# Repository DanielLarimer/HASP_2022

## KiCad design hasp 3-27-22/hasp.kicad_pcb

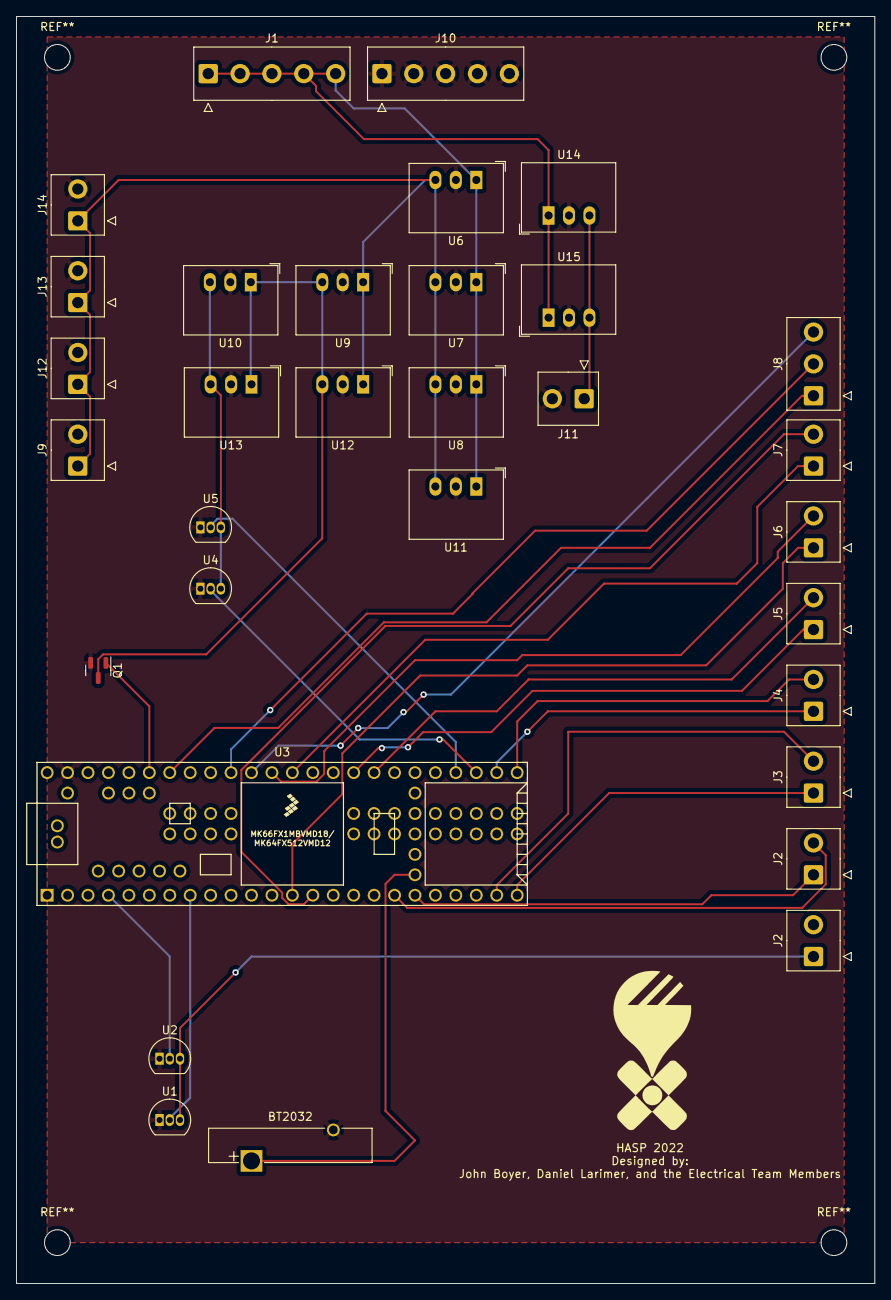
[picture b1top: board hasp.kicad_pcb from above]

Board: 2 copper layers, 106.7 x 157.5 mm, 33 parts (0 on the bottom side), 27 nets.

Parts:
 : LOGO; HASP 2022 KICAD
BT2032: Battery_Cell; Battery_Panasonic_CR2032-VS1N_Vertical_CircularHoles
J1, J10: Conn_01x05; TE_826576-5_1x05_P3.96mm_Vertical
J2, J2#2, J3, J4, J5, J6, J7: Conn_01x02; TE_826576-2_1x02_P3.96mm_Vertical
J8: Conn_01x03; TE_826576-3_1x03_P3.96mm_Vertical
J9: cam 1 Con; TE_826576-2_1x02_P3.96mm_Vertical
J11, J14: Cam 4 Con; TE_826576-2_1x02_P3.96mm_Vertical
J12: Cam 2 Con; TE_826576-2_1x02_P3.96mm_Vertical
J13: Cam 3 Con; TE_826576-2_1x02_P3.96mm_Vertical
Q1: BC818; SOT-23
U1, U2, U4, U5: DS18B20; TO-92_Inline
U3: Teensy3.6; Teensy35_36_All_Pins
U6, U7, U8, U11: R-78E12-0.5; Converter_DCDC_RECOM_R-78E-0.5_THT
U9, U12, U14, U15: R-78C5.0-1.0; Converter_DCDC_RECOM_R-78E-0.5_THT
U10, U13: R-78E3.3-1.0; Converter_DCDC_RECOM_R-78E-0.5_THT

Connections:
+3V3: J2.1, U1.3 (VDD), U2.3 (VDD), U4.3 (VDD), U5.3 (VDD), U10.3 (OUT), U13.3 (OUT)
+5V: J2.2, Q1.3 (C), U3.53 (VIN), U9.3 (OUT), U10.1 (IN), U12.3 (OUT), U13.1 (IN)
+12V: J9.1, J12.1, J13.1, J14.1, U6.3 (OUT), U7.3 (OUT), U8.3 (OUT), U9.1 (IN), U11.3 (OUT), U12.1 (IN)
+VDC: J1.1, J1.2, J1.3, J1.4, J1.5, U6.1 (IN), U7.1 (IN), U8.1 (IN), U11.1 (IN), U14.1 (IN), U15.1 (IN)
GND: BT2032.2 (-), J9.2, J10.1, J10.2, J10.3, J10.4, J10.5, J11.2, J12.2, J13.2, J14.2, Q1.2 (E), U1.1 (GND), U2.1 (GND), U3.1 (GND), U3.52 (AGND), U4.1 (GND), U5.1 (GND), U6.2 (GND), U7.2 (GND), U8.2 (GND), U9.2 (GND), U10.2 (GND), U11.2 (GND), U12.2 (GND), U13.2 (GND), U14.2 (GND), U15.2 (GND)
unnamed: BT2032.1 (+), U3.25 (VBAT)
unnamed: J2#2.1, U3.19 (27_RX1)
unnamed: J2#2.2, U3.18 (26_TX1)
unnamed: J3.1, U3.24 (32_A13_TX4_SCK1)
unnamed: J3.2, U3.23 (31_A12_RX4_CS1)
unnamed: J4.1, U3.31 (34_A15_RX5_CAN1RX_SDA0)
unnamed: J4.2, U3.30 (33_A14_TX5_CAN1TX_SCL0)
unnamed: J5.1, U3.38 (A22_DAC1)
unnamed: J5.2, U3.37 (A21_DAC0)
unnamed: J6.1, U3.13 (11_MOSI0)
unnamed: J6.2, U3.42 (15_A1_CS0_TOUCH)
unnamed: J7.1, U3.41 (14_A0_PWM_SCK0)
unnamed: J7.2, U3.14 (12_MISO0)
unnamed: J8.1, U3.47 (20_A6_PWM_CS0_SCK1)
unnamed: J8.2, U3.44 (17_A3_SDA0_TOUCH)
unnamed: J8.3, U3.43 (16_A2_SCL0_TOUCH)
unnamed: J11.1, U14.3 (OUT), U15.3 (OUT)
unnamed: Q1.1 (B), U3.48 (21_A7_PWM_CS0_SCK1)
unnamed: U1.2 (DQ), U3.8 (6_PWM)
unnamed: U2.2 (DQ), U3.4 (2_PWM)
unnamed: U3.32 (35_A16_PWM), U4.2 (DQ)
unnamed: U3.33 (36_A17_PWM), U5.2 (DQ)

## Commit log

2022-02-18 Add files via upload
    Initial Upload
2022-04-17 New files uploaded
2022-04-17 Old files
